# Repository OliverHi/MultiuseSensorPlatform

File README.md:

# MultiuseSensorPlatform
a mysensor based platform for a suite of different possible sensors

More information can be found [here](https://www.openhardware.io/view/261/OH-Mini-Multi-use-Sensor-Platform).

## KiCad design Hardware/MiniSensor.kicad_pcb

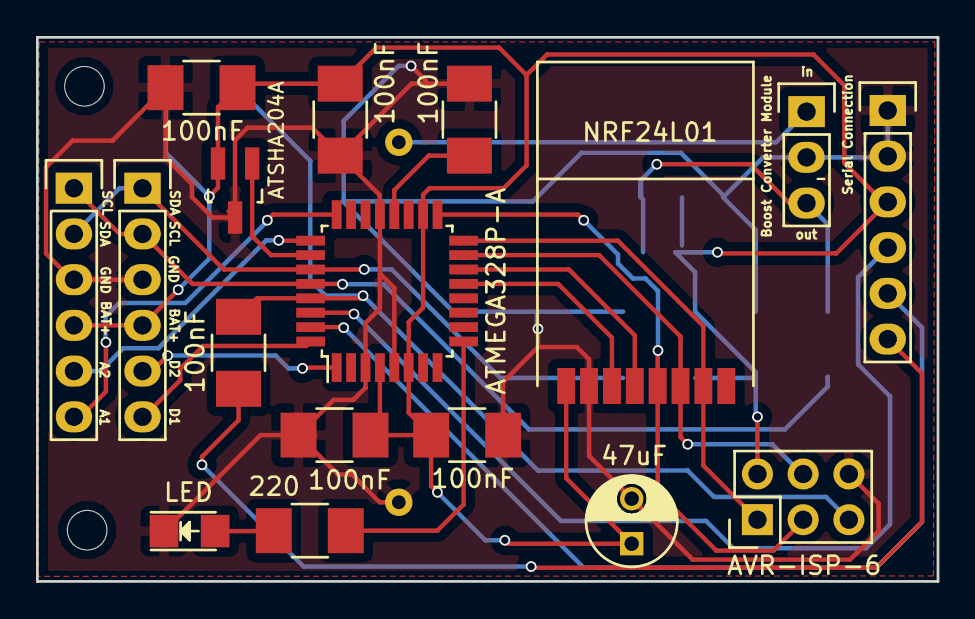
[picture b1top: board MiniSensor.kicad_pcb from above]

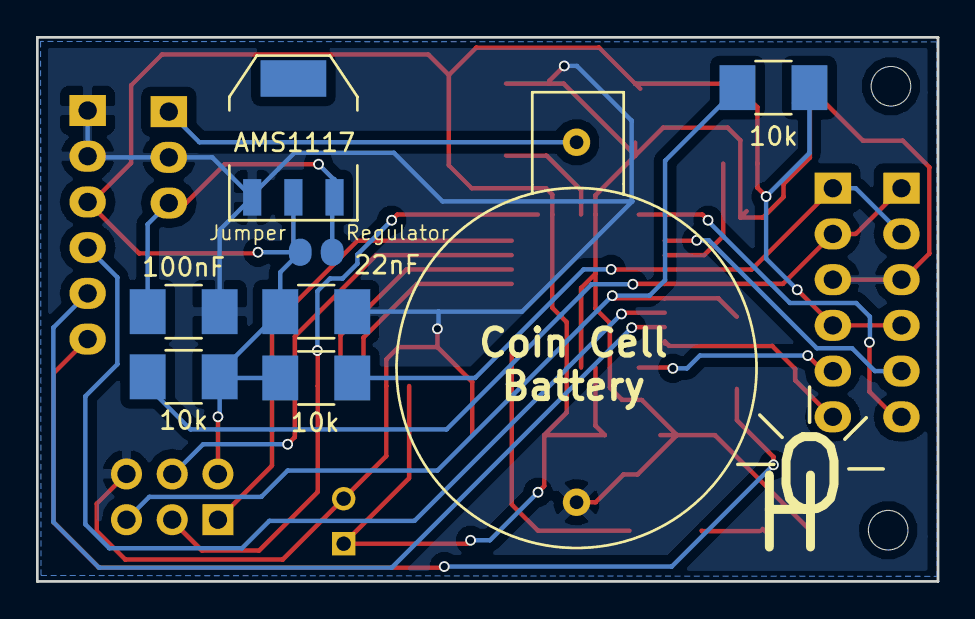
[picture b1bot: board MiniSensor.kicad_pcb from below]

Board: 2 copper layers, 50.0 x 30.2 mm, 25 parts (8 on the bottom side), 23 nets.

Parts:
BT1: Battery; CR2032 Battery Holder
C1, C2, C4, C5, C6, C8, C9: 100nF; C_1210_HandSoldering
C3: 22nF; C_1210_HandSoldering
C7: 47uF; C_Radial_D5_L6_P2.5
CON1: AVR-ISP-6; Pin_Header_Straight_2x03
D1: LED; LED_1206
IC1: ATMEGA328P-A; TQFP-32_7x7mm_Pitch0.8mm
JP1: JUMPER; 2_pin_solder_jumper_smd
P1: Boost Converter Module; Pin_Header_Straight_1x03
P2, P3, P4: CONN_01X06; Pin_Header_Straight_1x06
R1, R4, R5: 10k; R_1210_HandSoldering
R2: 220; R_1210_HandSoldering
U1: AMS1117; SOT-223
U3: NRF24L01; NRF24L01-SMD
U4: ATSHA204A; SOT-23_Handsoldering

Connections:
+BATT: C3.1, C5.1, C6.1, C7.1, C8.1, C9.1, CON1.2, IC1.4, IC1.6, IC1.18, JP1.2, P2.4, P3.4, P4.3, R1.2, R4.2, R5.2, U1.2, U3.2, U4.2
A1: IC1.24, P3.6
A2: IC1.25, P3.5
A3: IC1.26, U4.1
CE: IC1.13, U3.3
CSN: IC1.14, U3.4
D2/Int0: IC1.32, P2.6
D3/Int1: IC1.1, P2.5
D5: IC1.9, R2.1
DTR: C4.1, P4.6
GND: BT1.2, C1.2, C2.2, C3.2, C5.2, C6.2, C7.2, C8.2, C9.2, CON1.6, D1.1, IC1.3, IC1.5, IC1.21, P1.2, P2.3, P3.3, P4.1, P4.2, U1.1, U3.1, U4.3
MISO: CON1.1, IC1.16, U3.7
MOSI: CON1.4, IC1.15, U3.6
unnamed: BT1.1, P1.1
unnamed: C1.1, IC1.20
unnamed: C2.1, JP1.1, P1.3, U1.3
unnamed: D1.2, R2.2
RX: IC1.30, P4.4
Reset: C4.2, CON1.5, IC1.29, R1.1
SCK: CON1.3, IC1.17, U3.5
SCL: IC1.28, P2.2, P3.1, R5.1
SDA: IC1.27, P2.1, P3.2, R4.1
TX: IC1.31, P4.5

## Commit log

2016-05-19 added first version of the schematics
2016-06-21 updated schematics, moved to hardware folder
2016-06-21 version 1 of software for soil moisture added
2016-07-04 schematics updated to final version 1, gerber export added
2016-07-04 added more debugging to soilmoisture sketch
2016-09-16 added sketch for a motion sensor
2016-10-02 added some pictures of my build
2016-10-02 added voltage readings to motion sketch, the sketch now also sends an off signal right after an on signal instead of letting the controller do that
2016-10-27 updated documentation, added button/door sketch
2016-10-27 added simple debouncing to the button/door sketch
2016-11-12 updated sketches to mySensors 2, moved old sketches to other folder
2016-11-13 added signing to all sketches, added temperature/humidity sketch
2017-03-13 added signing support lines to sketches, updated door/button and temp/hum sketches
2017-03-13 Update ButtonDoor.ino
    Fixed name
2019-01-08 added link to project on openhardware.io to readme
